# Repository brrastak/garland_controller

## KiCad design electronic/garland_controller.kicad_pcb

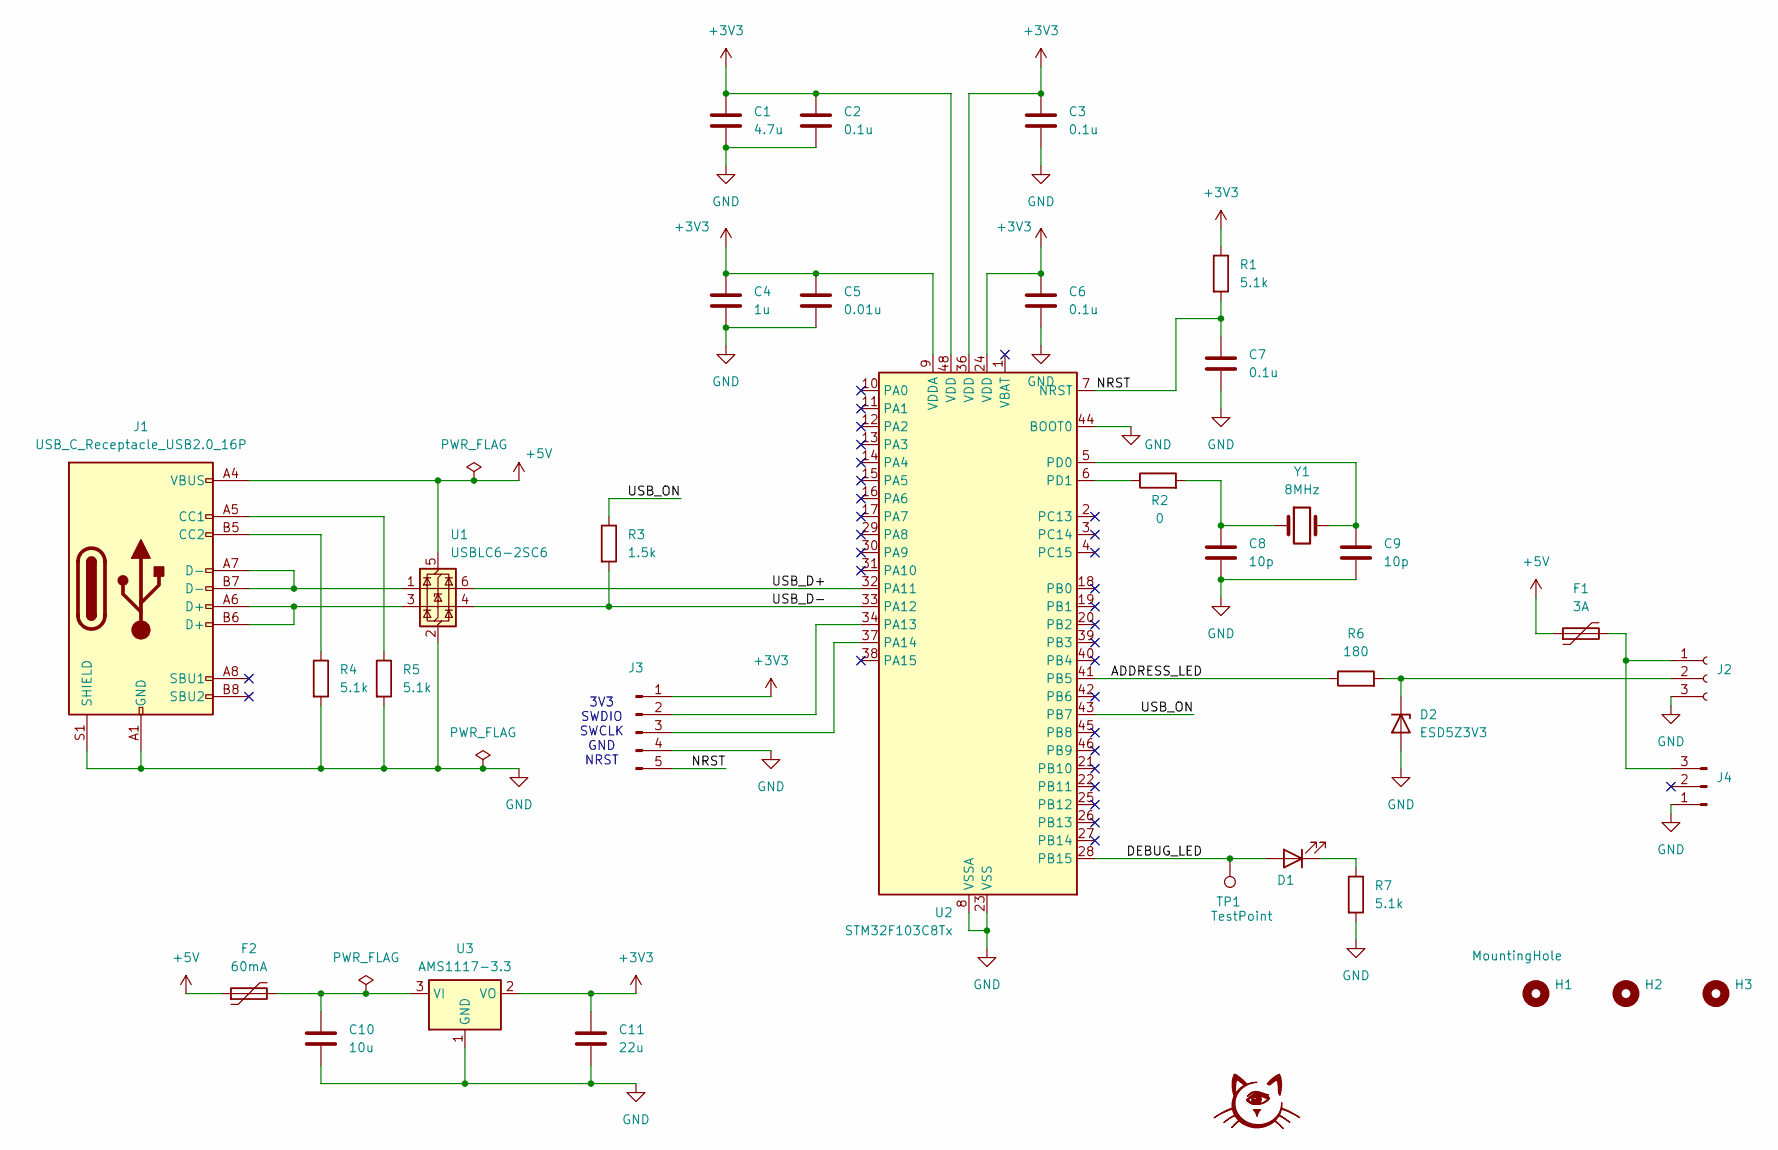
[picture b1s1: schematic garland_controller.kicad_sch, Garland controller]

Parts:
C1: 4.7u; C_1206_3216Metric_Pad1.33x1.80mm_HandSolder
C2, C3, C6, C7: 0.1u; C_0603_1608Metric_Pad1.08x0.95mm_HandSolder
C4: 1u; C_0603_1608Metric_Pad1.08x0.95mm_HandSolder
C5: 0.01u; C_0603_1608Metric_Pad1.08x0.95mm_HandSolder
C8, C9: 10p; C_0603_1608Metric_Pad1.08x0.95mm_HandSolder
C10: 10u; C_1206_3216Metric_Pad1.33x1.80mm_HandSolder
C11: 22u; C_1206_3216Metric_Pad1.33x1.80mm_HandSolder
D1: LED; LED_0603_1608Metric_Pad1.05x0.95mm_HandSolder
D2: ESD5Z3V3; D_SOD-523
F1: 3A; Fuse_1210_3225Metric_Pad1.42x2.65mm_HandSolder
F2: 60mA; Fuse_0805_2012Metric_Pad1.15x1.40mm_HandSolder
G1: stamp
H1, H2, H3: MountingHole; MountingHole_2.1mm
J1: USB_C_Receptacle_USB2.0_16P; USB_C_Receptacle_GCT_USB4105-xx-A_16P_TopMnt_Horizontal
J2: Conn_01x03_Socket; PinHeader_1x03_P2.54mm_Vertical
J3: Conn_01x05_Pin; PinHeader_1x05_P2.54mm_Vertical
J4: Conn_01x03_Pin; PinHeader_1x03_P2.54mm_Vertical
R1, R4, R5, R7: 5.1k; R_0603_1608Metric_Pad0.98x0.95mm_HandSolder
R2: 0; R_0603_1608Metric_Pad0.98x0.95mm_HandSolder
R3: 1.5k; R_0603_1608Metric_Pad0.98x0.95mm_HandSolder
R6: 180; R_0603_1608Metric_Pad0.98x0.95mm_HandSolder
TP1: TestPoint; PinHeader_1x01_P2.54mm_Vertical
U1: USBLC6-2SC6; SOT-23-6
U2: STM32F103C8Tx; LQFP-48_7x7mm_P0.5mm
U3: AMS1117-3.3; SOT-223-3_TabPin2
Y1: 8MHz; Crystal_SMD_HC49-SD

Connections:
+3V3: C1.1, C2.1, C3.1, C4.1, C5.1, C6.1, C11.1, J3.1, R1.1, U2.9 (VDDA), U2.24 (VDD), U2.36 (VDD), U2.48 (VDD), U3.2 (VO)
+5V: F1.1, F2.1, J1.A4 (VBUS), J1.A9 (VBUS), J1.B4 (VBUS), J1.B9 (VBUS), U1.5 (VBUS)
/ADDRESS_LED: R6.1, U2.41 (PB5)
/DEBUG_LED: D1.2 (A), TP1.1, U2.28 (PB15)
/NRST: C7.1, J3.5, R1.2, U2.7 (NRST)
/USB_D+: U1.6 (I/O1), U2.32 (PA11)
/USB_D-: R3.2, U1.4 (I/O2), U2.33 (PA12)
/USB_ON: R3.1, U2.43 (PB7)
GND: C1.2, C2.2, C3.2, C4.2, C5.2, C6.2, C7.2, C8.2, C9.2, C10.2, C11.2, D2.2 (A), J1.A1 (GND), J1.A12 (GND), J1.B1 (GND), J1.B12 (GND), J1.S1 (SHIELD), J2.3, J3.4, J4.1, R4.2, R5.2, R7.2, U1.2 (GND), U2.8 (VSSA), U2.23 (VSS), U2.35 (VSS), U2.44 (BOOT0), U2.47 (VSS), U3.1 (GND)
unnamed: C8.1, R2.2, Y1.1
unnamed: D1.1 (K), R7.1
unnamed: D2.1 (K), J2.2, R6.2
unnamed: J1.A5 (CC1), R5.1
unnamed: J1.B5 (CC2), R4.1
unnamed: J1.A6 (D+), J1.B6 (D+), U1.3 (I/O2)
unnamed: J1.A7 (D-), J1.B7 (D-), U1.1 (I/O1)
unnamed: F1.2, J2.1, J4.3
unnamed: J3.2, U2.34 (PA13)
unnamed: J3.3, U2.37 (PA14)
unnamed: C9.1, U2.5 (PD0), Y1.2
unnamed: R2.1, U2.6 (PD1)
unnamed: C10.1, F2.2, U3.3 (VI)

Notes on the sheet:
3V3 SWDIO SWCLK GND NRST

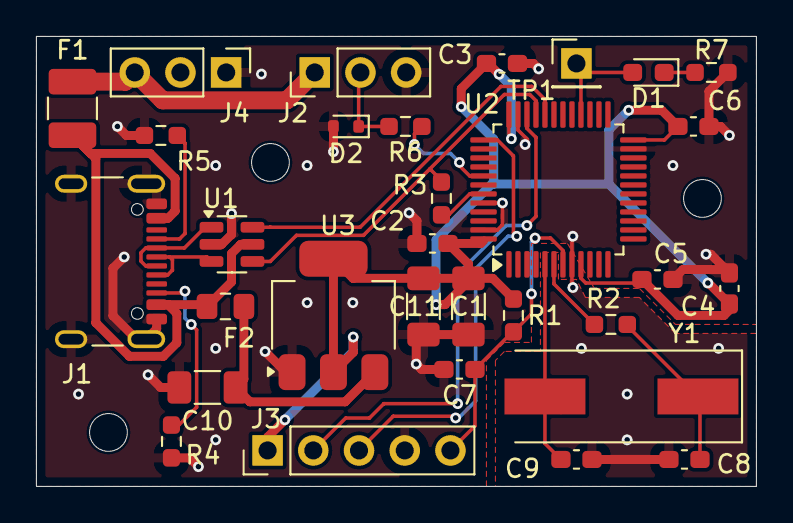
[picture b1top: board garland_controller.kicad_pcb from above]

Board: 2 copper layers, 40.0 x 25.0 mm, 35 parts (1 on the bottom side), 22 nets.

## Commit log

2025-02-09 Init schematic
2025-02-09 Place components
2025-02-09 Add generated box and lid
2025-02-09 Import box to FreeCAD
2025-02-09 Tune fuses
2025-02-09 Layout rev. 0.1
2025-02-10 Add gerber files
2025-03-18 Add firmware
2025-03-19 Update dependencies
2025-03-19 Add license
2025-03-19 Move holes and add ridges
2025-03-19 Export box and lid in .step format
